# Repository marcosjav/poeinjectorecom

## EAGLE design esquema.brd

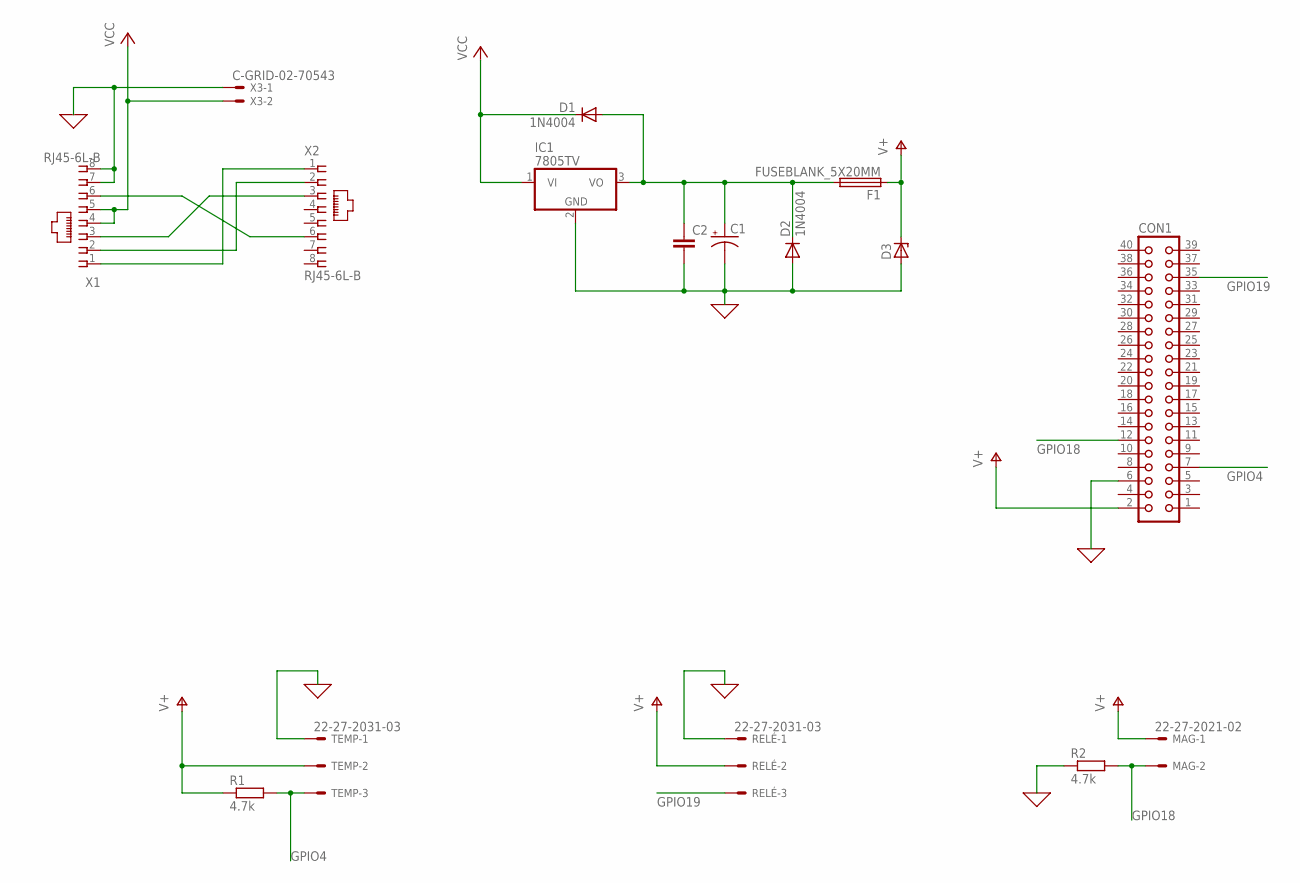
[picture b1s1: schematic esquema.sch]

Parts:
C1: CPOL-USE5-8.5; E5-8,5
C2: C-EU025-030X050; C025-030X050
CON1: CON40
D1, D2: 1N4004; DO41-10
D3: ZENER-DIODEDO35Z10; DO35Z10
F1: FUSEBLANK_5X20MM; FUSE_HOLDER_5X20MM
IC1: 7805TV; TO220V
MAG: 22-27-2021-02; 6410-02
R1, R2: 4.7k; 0204/7
RELÉ: 22-27-2031-03; 6410-03
TEMP: 22-27-2031-03; 6410-03
X1, X2: RJ45-6L-B; RJ45-NO-SHIELD
X3: C-GRID-02-70543; 70543-02

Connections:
0: C1.-, C2.2, CON1.6, D2.A, D3.A, IC1.2 (GND), R2.1, RELÉ.1, TEMP.1, X1.7, X1.8, X3.1
GPIO4: CON1.7, R1.2, TEMP.3
GPIO18: CON1.12, MAG.2, R2.2
GPIO19: CON1.35, RELÉ.3
unnamed: X1.6, X2.6
unnamed: C1.+, C2.1, D1.A, D2.C, F1.2, IC1.3 (VO)
unnamed: X1.3, X2.3
unnamed: X1.2, X2.2
unnamed: X1.1, X2.1
V+: CON1.2, D3.C, F1.1, MAG.1, R1.1, RELÉ.2, TEMP.2
VCC: D1.C, IC1.1 (VI), X1.4, X1.5, X3.2

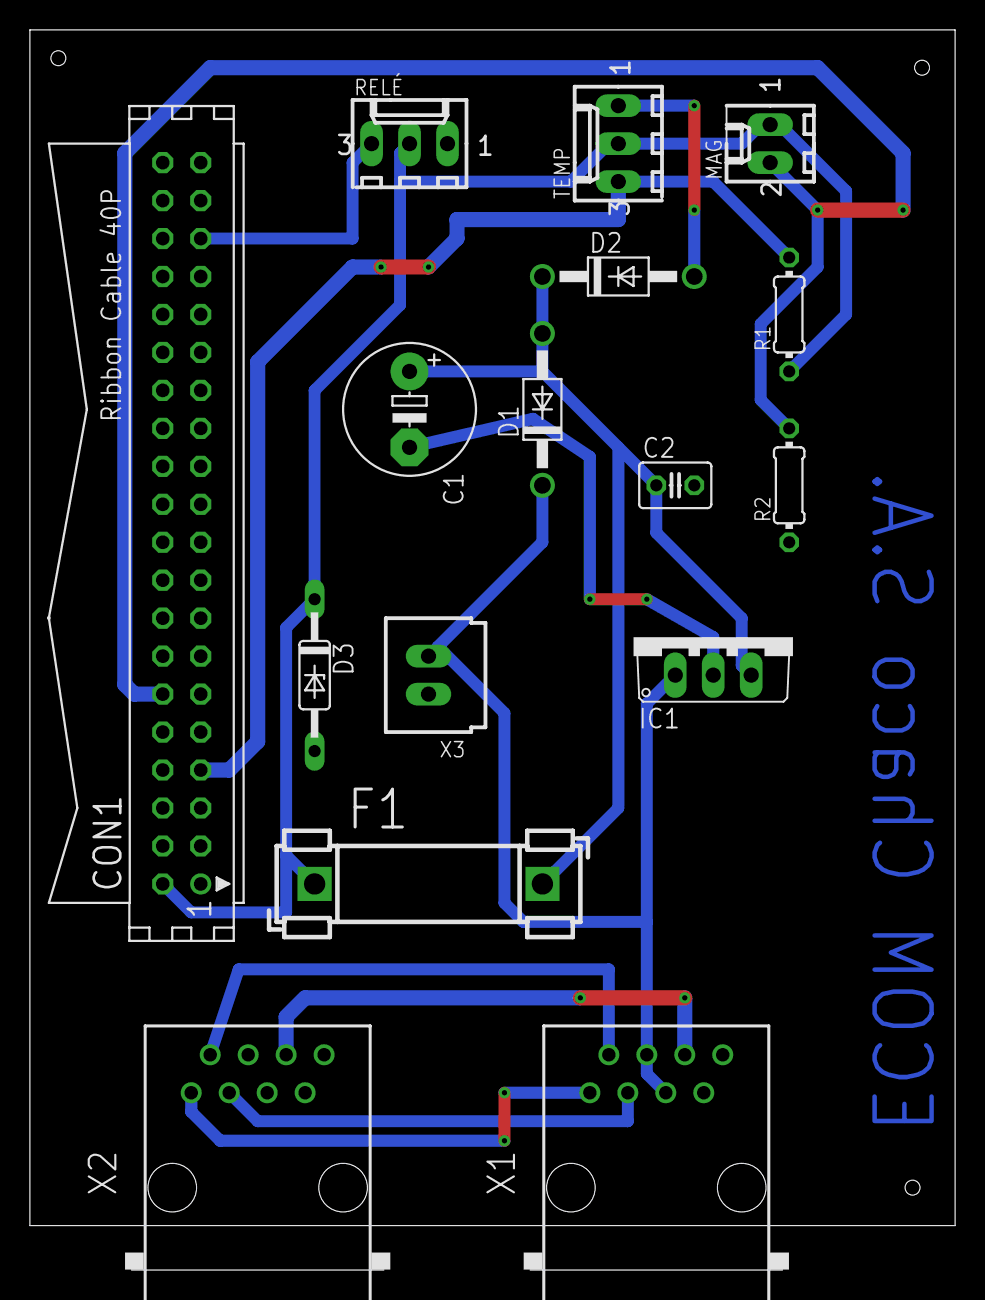
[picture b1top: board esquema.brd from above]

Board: 2 copper layers, 61.9 x 83.0 mm, 16 parts (0 on the bottom side), 11 nets.

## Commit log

2019-03-15 poe injector board for Ecom SA
